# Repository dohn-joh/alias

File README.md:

# Alias

## Features
- Custom 3D printed keycaps
  - [Lever keycaps](https://github.com/dohn-joh/keycaps)
  - [Low profile DES variant](https://github.com/dohn-joh/PseudoMakeMeKeyCapProfiles)
- Choc v1 and v2 compatible hotswap
- [Wireless dongle](https://github.com/dohn-joh/dongle-zmk)
- PCB generated in [ergogen](https://github.com/ergogen/ergogen)

## Compatibility/Disclaimer
Everything in this repo has been tested. Even so, use these files at your own risk. 
If you decide to have the pcb fabbed, 1.2mm pcb thickness is recommended. Higher thicknesses are still compatible but add height to the case.

- **Status of keycap compatibility**: only keycaps that are <=17.85mm wide and <=18mm deep are supported
- **Status of bottom case**: ~~cutouts are currently only compatible with choc v2 with the exception of the lever keys, which have cutouts that support both choc v1 and v2~~ fully compatible with both choc v1 and v2

## Parts
|Part: Model#|Link|
|-|-|
|Microcontroller: Supermini NRF52840 (or nice!nano)||
|Battery: 301230 with molex pico ezmate connector||
|Battery connector: molex pico ezmate 1x02||
|Power button: PCM12SMTR||
|Reset button: SKHLLCA010||
|Choc v1 or v2 switches x 36||
|Kailh Choc PG1350 Hot Swap Sockets x 36||
|Keycaps||
|Magnetic USB connector (optional): Netdot Gen10||

## Thanks
These people and many more helped make this keyboard possible. Yall are legends.
```
MrZealot
Pseudoku
petejohanson
caksoylar(bravekarma)
jcmkk3
ceoloide
infused-kim
Flatfootfox
sadekbaroudi
zzeneg
joelspadin
wolfwood
claussen
Geist
rmwphd(atinyzubat)
fish
Araxia
honorless
elkepenin
```

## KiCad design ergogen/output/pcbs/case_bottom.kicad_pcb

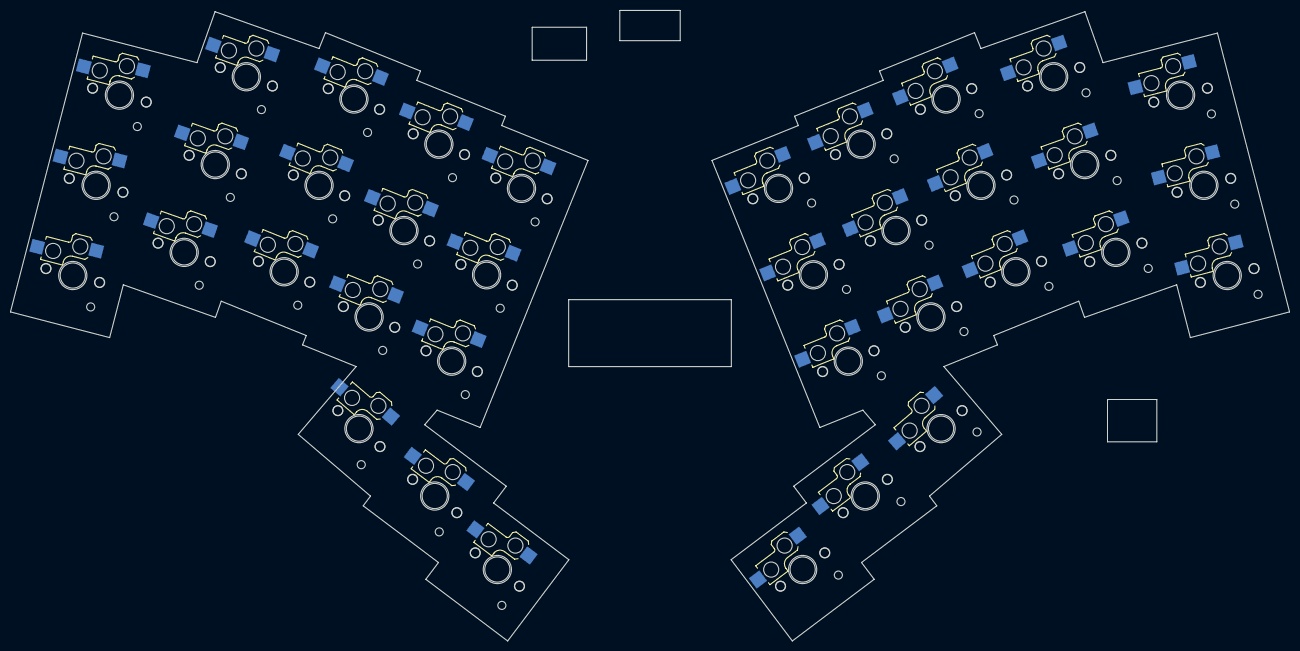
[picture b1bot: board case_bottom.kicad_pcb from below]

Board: 2 copper layers, 254.0 x 125.2 mm, 36 parts (36 on the bottom side), 5 nets, no tracks yet.

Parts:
S1, S2, S3, S4, S5, S6, S7, S8, S9, S10, S11, S12, S13, S14, S15, S16, S17, S18, S19, S20, S21, S22, S23, S24, S25, S26, S27, S28, S29, S30, S31, S32, S33, S34, S35, S36: switch_choc_v1_v2

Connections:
C0: S1.1, S2.1, S3.1, S16.1, S17.1, S18.1
C1: S4.1, S5.1, S6.1, S19.1, S20.1, S21.1
C2: S7.1, S8.1, S9.1, S22.1, S23.1, S24.1, S31.1, S34.1
C3: S10.1, S11.1, S12.1, S25.1, S26.1, S27.1, S32.1, S35.1
C4: S13.1, S14.1, S15.1, S28.1, S29.1, S30.1, S33.1, S36.1

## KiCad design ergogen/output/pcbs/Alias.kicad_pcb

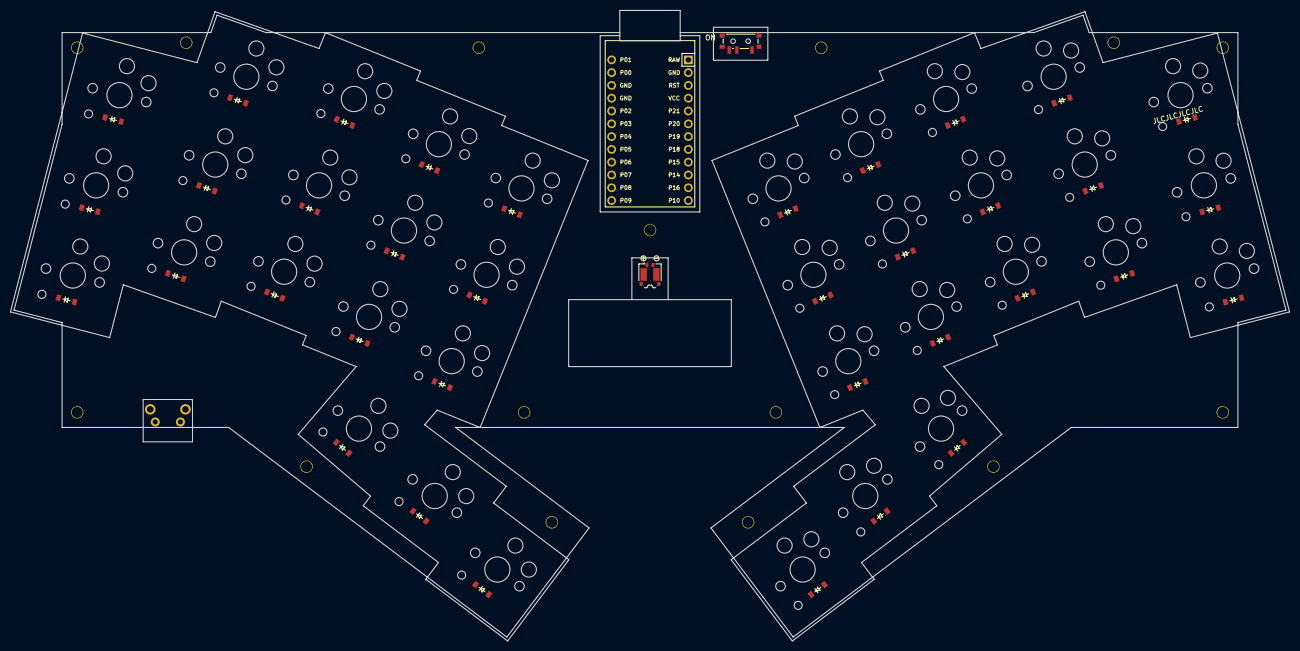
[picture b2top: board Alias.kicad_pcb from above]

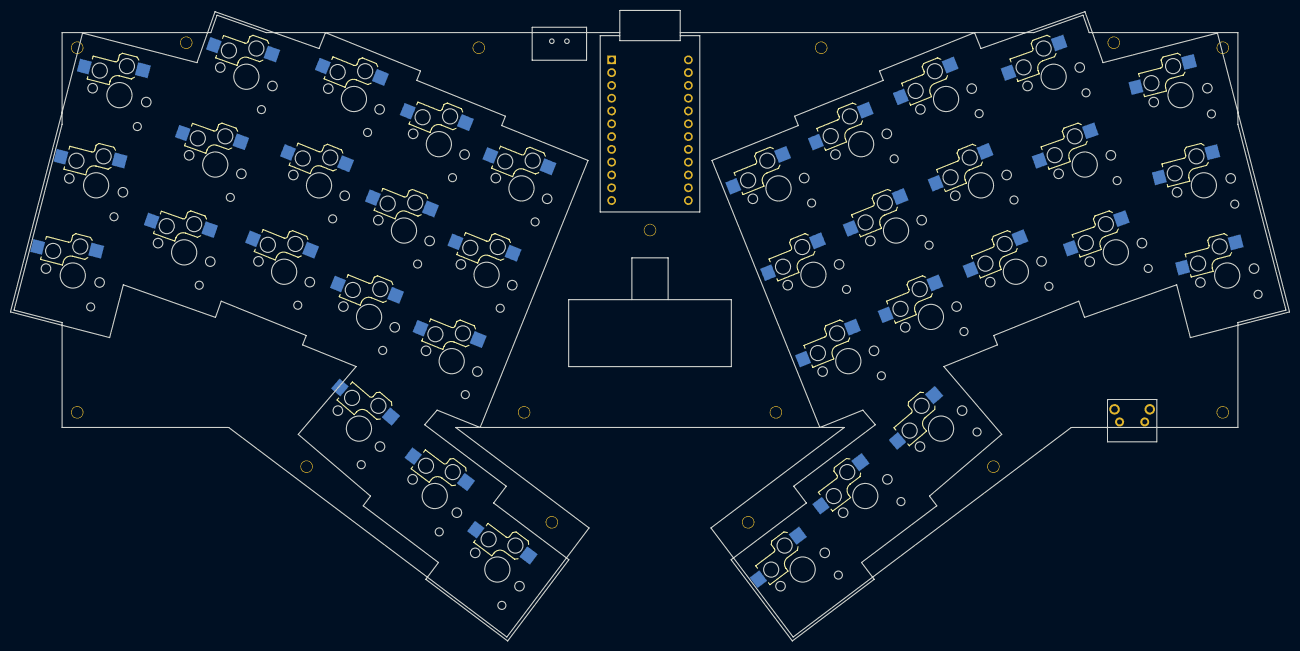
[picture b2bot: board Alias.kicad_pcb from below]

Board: 2 copper layers, 254.0 x 125.2 mm, 93 parts (36 on the bottom side), 53 nets, no tracks yet.

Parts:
CONN1: conn_molex_pico_ezmate_1x02
D1, D2, D3, D4, D5, D6, D7, D8, D9, D10, D11, D12, D13, D14, D15, D16, D17, D18, D19, D20, D21, D22, D23, D24, D25, D26, D27, D28, D29, D30, D31, D32, D33, D34, D35, D36: ComboDiode
H1, H2, H3, H4, H5, H6, H7, H8, H9, H10, H11, H12, H13, H14, H15: mounting_hole
ICON1: icon_bat
MCU1: ProMicro
PAD1: pads
S1, S2, S3, S4, S5, S6, S7, S8, S9, S10, S11, S12, S13, S14, S15, S16, S17, S18, S19, S20, S21, S22, S23, S24, S25, S26, S27, S28, S29, S30, S31, S32, S33, S34, S35, S36: switch_choc_v1_v2
S37: SKHLLCA010
SW1: power_switch

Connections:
BAT_P: CONN1.1, PAD1.1, SW1.3
C0: MCU1.17, S1.1, S2.1, S3.1, S16.1, S17.1, S18.1
C1: MCU1.18, S4.1, S5.1, S6.1, S19.1, S20.1, S21.1
C2: MCU1.19, S7.1, S8.1, S9.1, S22.1, S23.1, S24.1, S31.1, S34.1
C3: MCU1.20, S10.1, S11.1, S12.1, S25.1, S26.1, S27.1, S32.1, S35.1
C4: MCU1.21, S13.1, S14.1, S15.1, S28.1, S29.1, S30.1, S33.1, S36.1
GND: CONN1.2, MCU1.2, MCU1.15, MCU1.16, PAD1.2, S37.2
R0: D3.1, D6.1, D9.1, D12.1, D15.1, MCU1.5
R1: D2.1, D5.1, D8.1, D11.1, D14.1, MCU1.6
R2: D1.1, D4.1, D7.1, D10.1, D13.1, MCU1.7
R3: D31.1, D32.1, D33.1, MCU1.8
R4: D18.1, D21.1, D24.1, D27.1, D30.1, MCU1.9
R5: D17.1, D20.1, D23.1, D26.1, D29.1, MCU1.10
R6: D16.1, D19.1, D22.1, D25.1, D28.1, MCU1.11
R7: D34.1, D35.1, D36.1, MCU1.12
RAW: MCU1.1, SW1.2
RST: MCU1.3, S37.1
base_cluster: D32.2, S32.2
extension_cluster: D33.2, S33.2
flexion_cluster: D31.2, S31.2
index_bottom: D10.2, S10.2
index_home: D11.2, S11.2
index_top: D12.2, S12.2
inner_bottom: D13.2, S13.2
inner_home: D14.2, S14.2
inner_top: D15.2, S15.2
middle_bottom: D7.2, S7.2
middle_home: D8.2, S8.2
middle_top: D9.2, S9.2
mirror_base_cluster: D35.2, S35.2
mirror_extension_cluster: D36.2, S36.2
mirror_flexion_cluster: D34.2, S34.2
mirror_index_bottom: D25.2, S25.2
mirror_index_home: D26.2, S26.2
mirror_index_top: D27.2, S27.2
mirror_inner_bottom: D28.2, S28.2
mirror_inner_home: D29.2, S29.2
mirror_inner_top: D30.2, S30.2
mirror_middle_bottom: D22.2, S22.2
mirror_middle_home: D23.2, S23.2
mirror_middle_top: D24.2, S24.2
mirror_pinky_bottom: D16.2, S16.2
mirror_pinky_home: D17.2, S17.2
mirror_pinky_top: D18.2, S18.2
mirror_ring_bottom: D19.2, S19.2
mirror_ring_home: D20.2, S20.2
mirror_ring_top: D21.2, S21.2
pinky_bottom: D1.2, S1.2
pinky_home: D2.2, S2.2
pinky_top: D3.2, S3.2
ring_bottom: D4.2, S4.2
ring_home: D5.2, S5.2
ring_top: D6.2, S6.2

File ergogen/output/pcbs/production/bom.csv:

Designator,Footprint,Quantity,Value,LCSC Part #
CONN1,conn_molex_pico_ezmate_1x02,1,,
"D1, D10, D11, D12, D13, D14, D15, D16, D17, D18, D19, D2, D20, D21, D22, D23, D24, D25, D26, D27, D28, D29, D3, D30, D31, D32, D33, D34, D35, D36, D4, D5, D6, D7, D8, D9",ComboDiode,36,,
"H1, H10, H11, H12, H13, H14, H15, H2, H3, H4, H5, H6, H7, H8, H9",mounting_hole,15,,
MCU1,ProMicro,1,,
PAD1,pads,1,,
S37,SKHLLCA010,1,SKHLLCA010,
SW1,power_switch,1,,

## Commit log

2024-06-20 update everything
2024-06-20 Create LICENSE
2024-06-20 update license
2024-06-22 update photos
2024-09-03 update case compatibility
